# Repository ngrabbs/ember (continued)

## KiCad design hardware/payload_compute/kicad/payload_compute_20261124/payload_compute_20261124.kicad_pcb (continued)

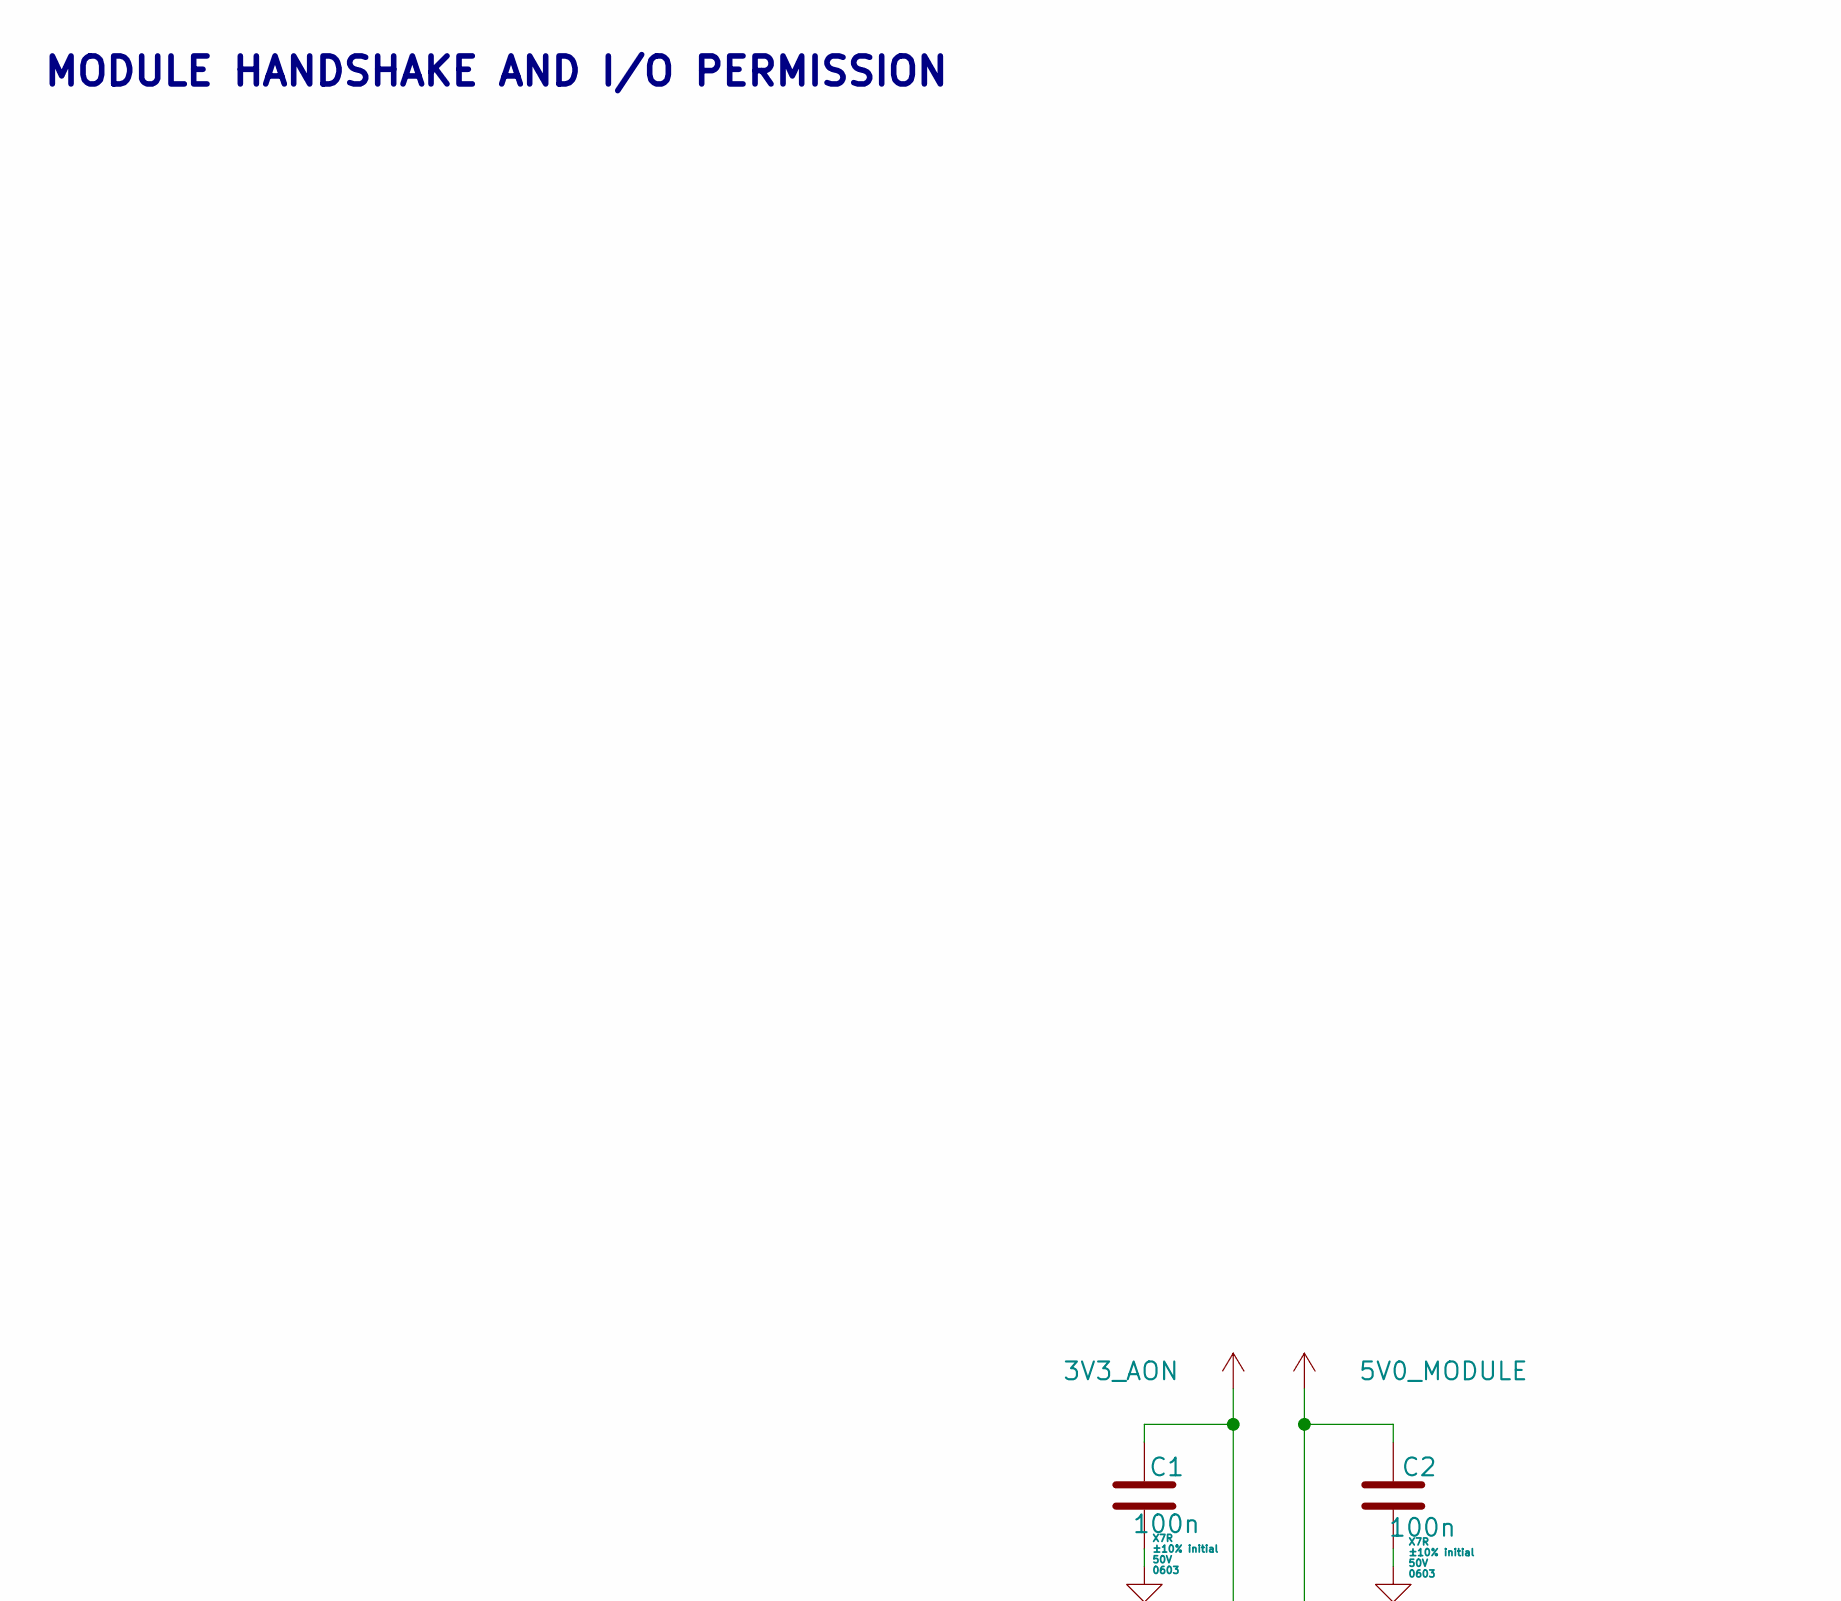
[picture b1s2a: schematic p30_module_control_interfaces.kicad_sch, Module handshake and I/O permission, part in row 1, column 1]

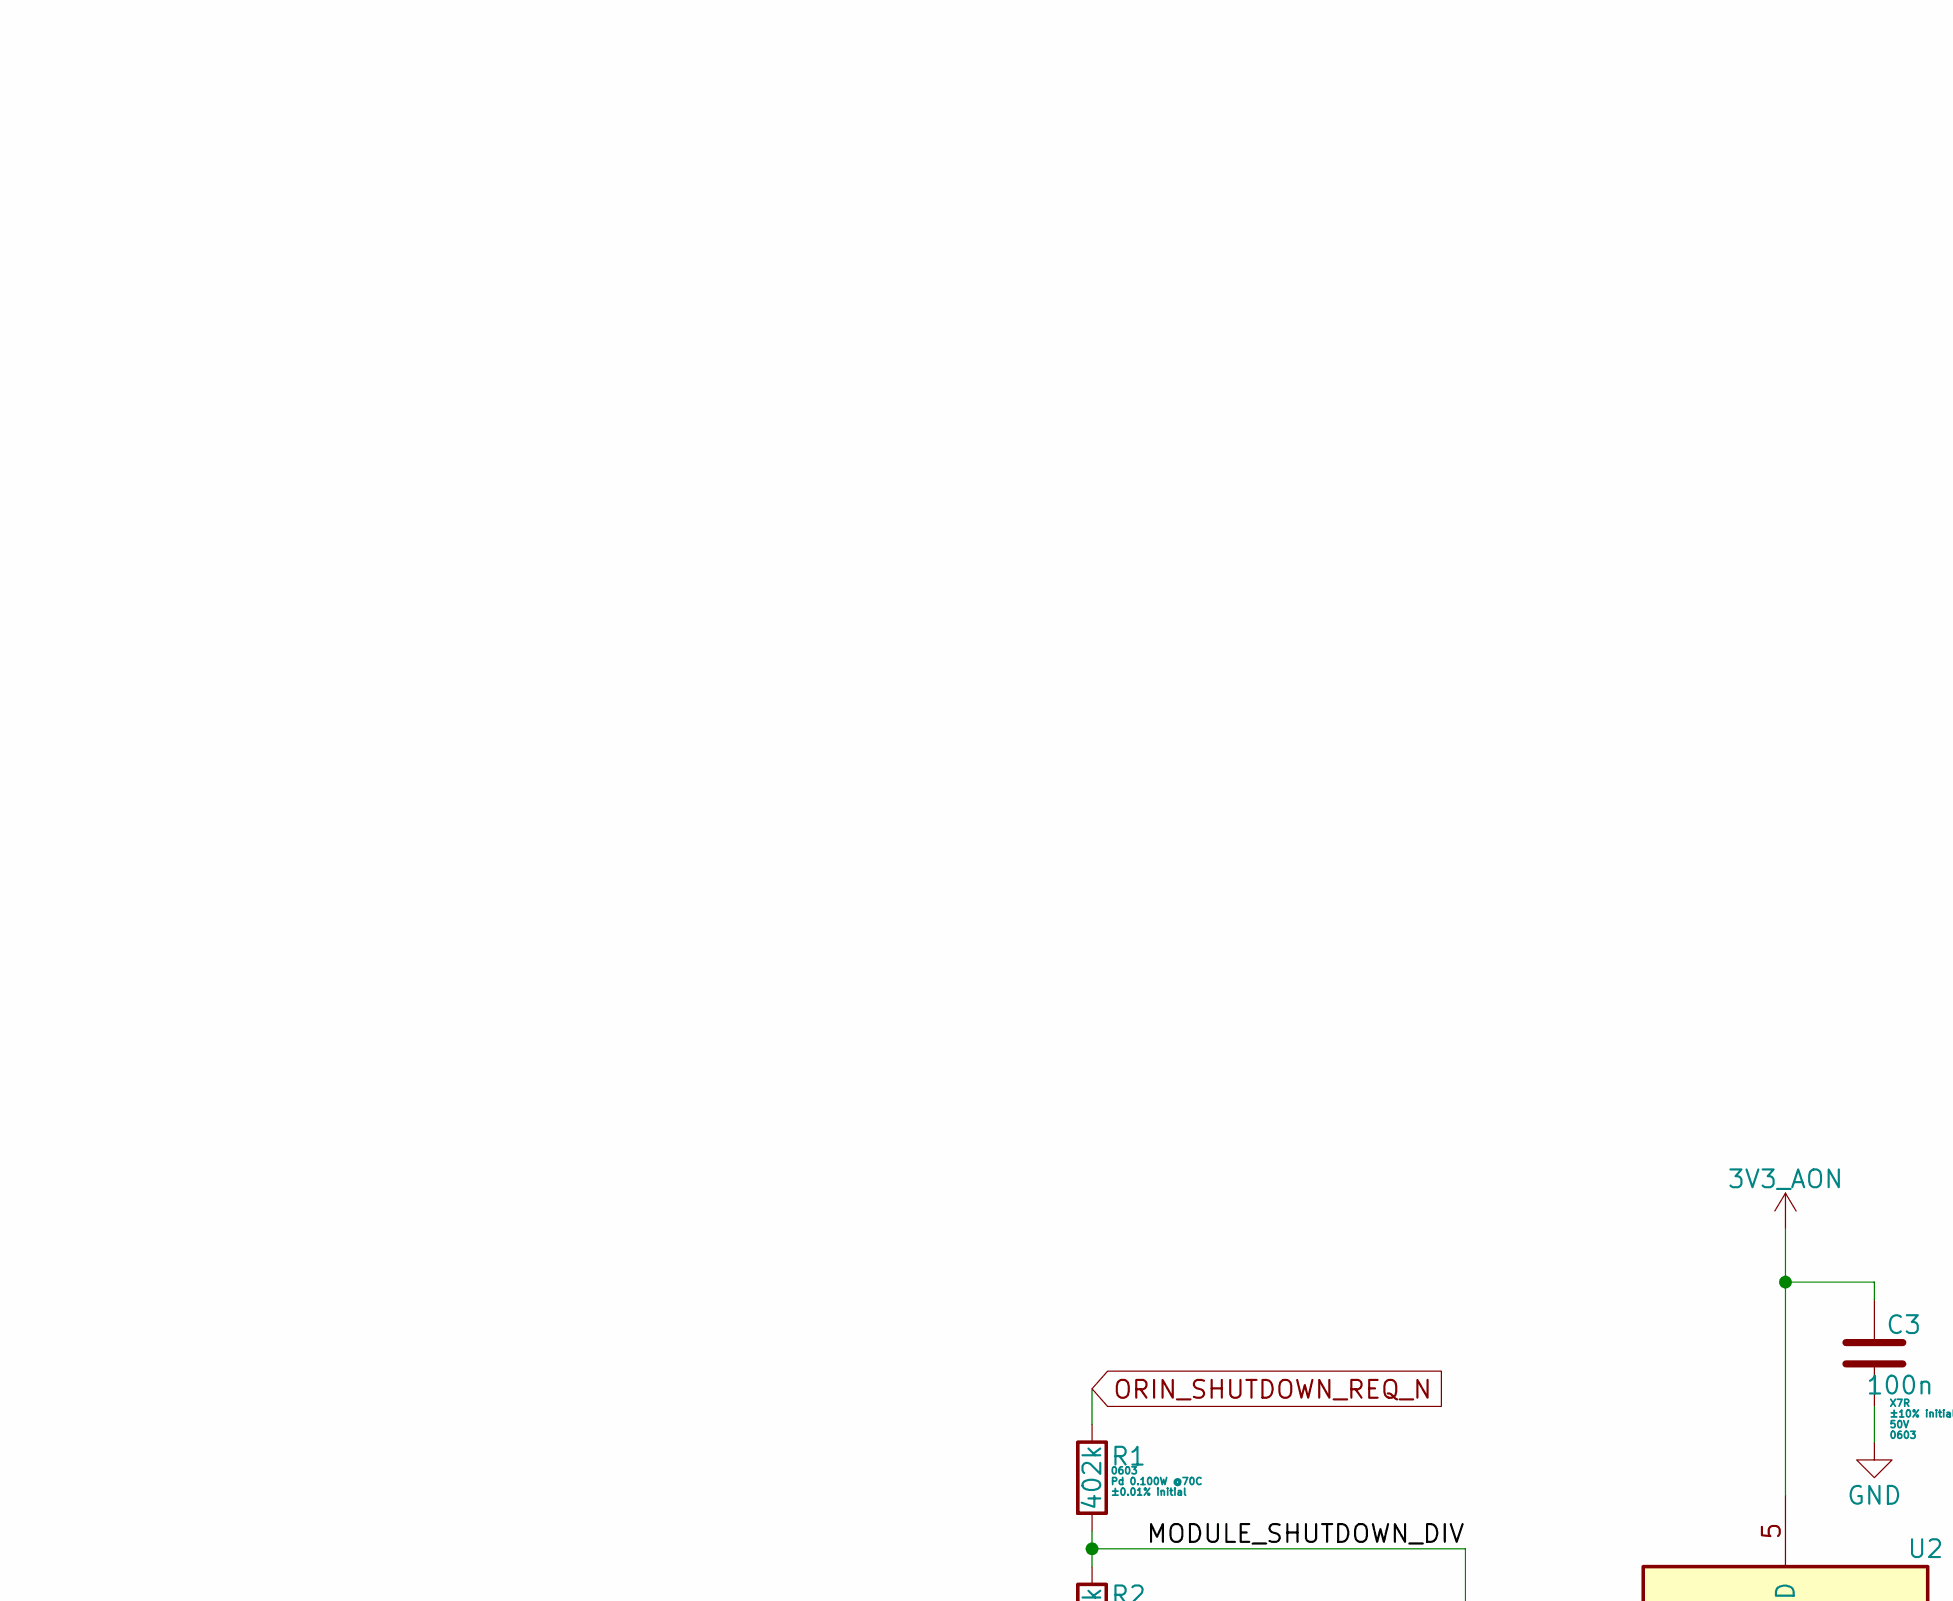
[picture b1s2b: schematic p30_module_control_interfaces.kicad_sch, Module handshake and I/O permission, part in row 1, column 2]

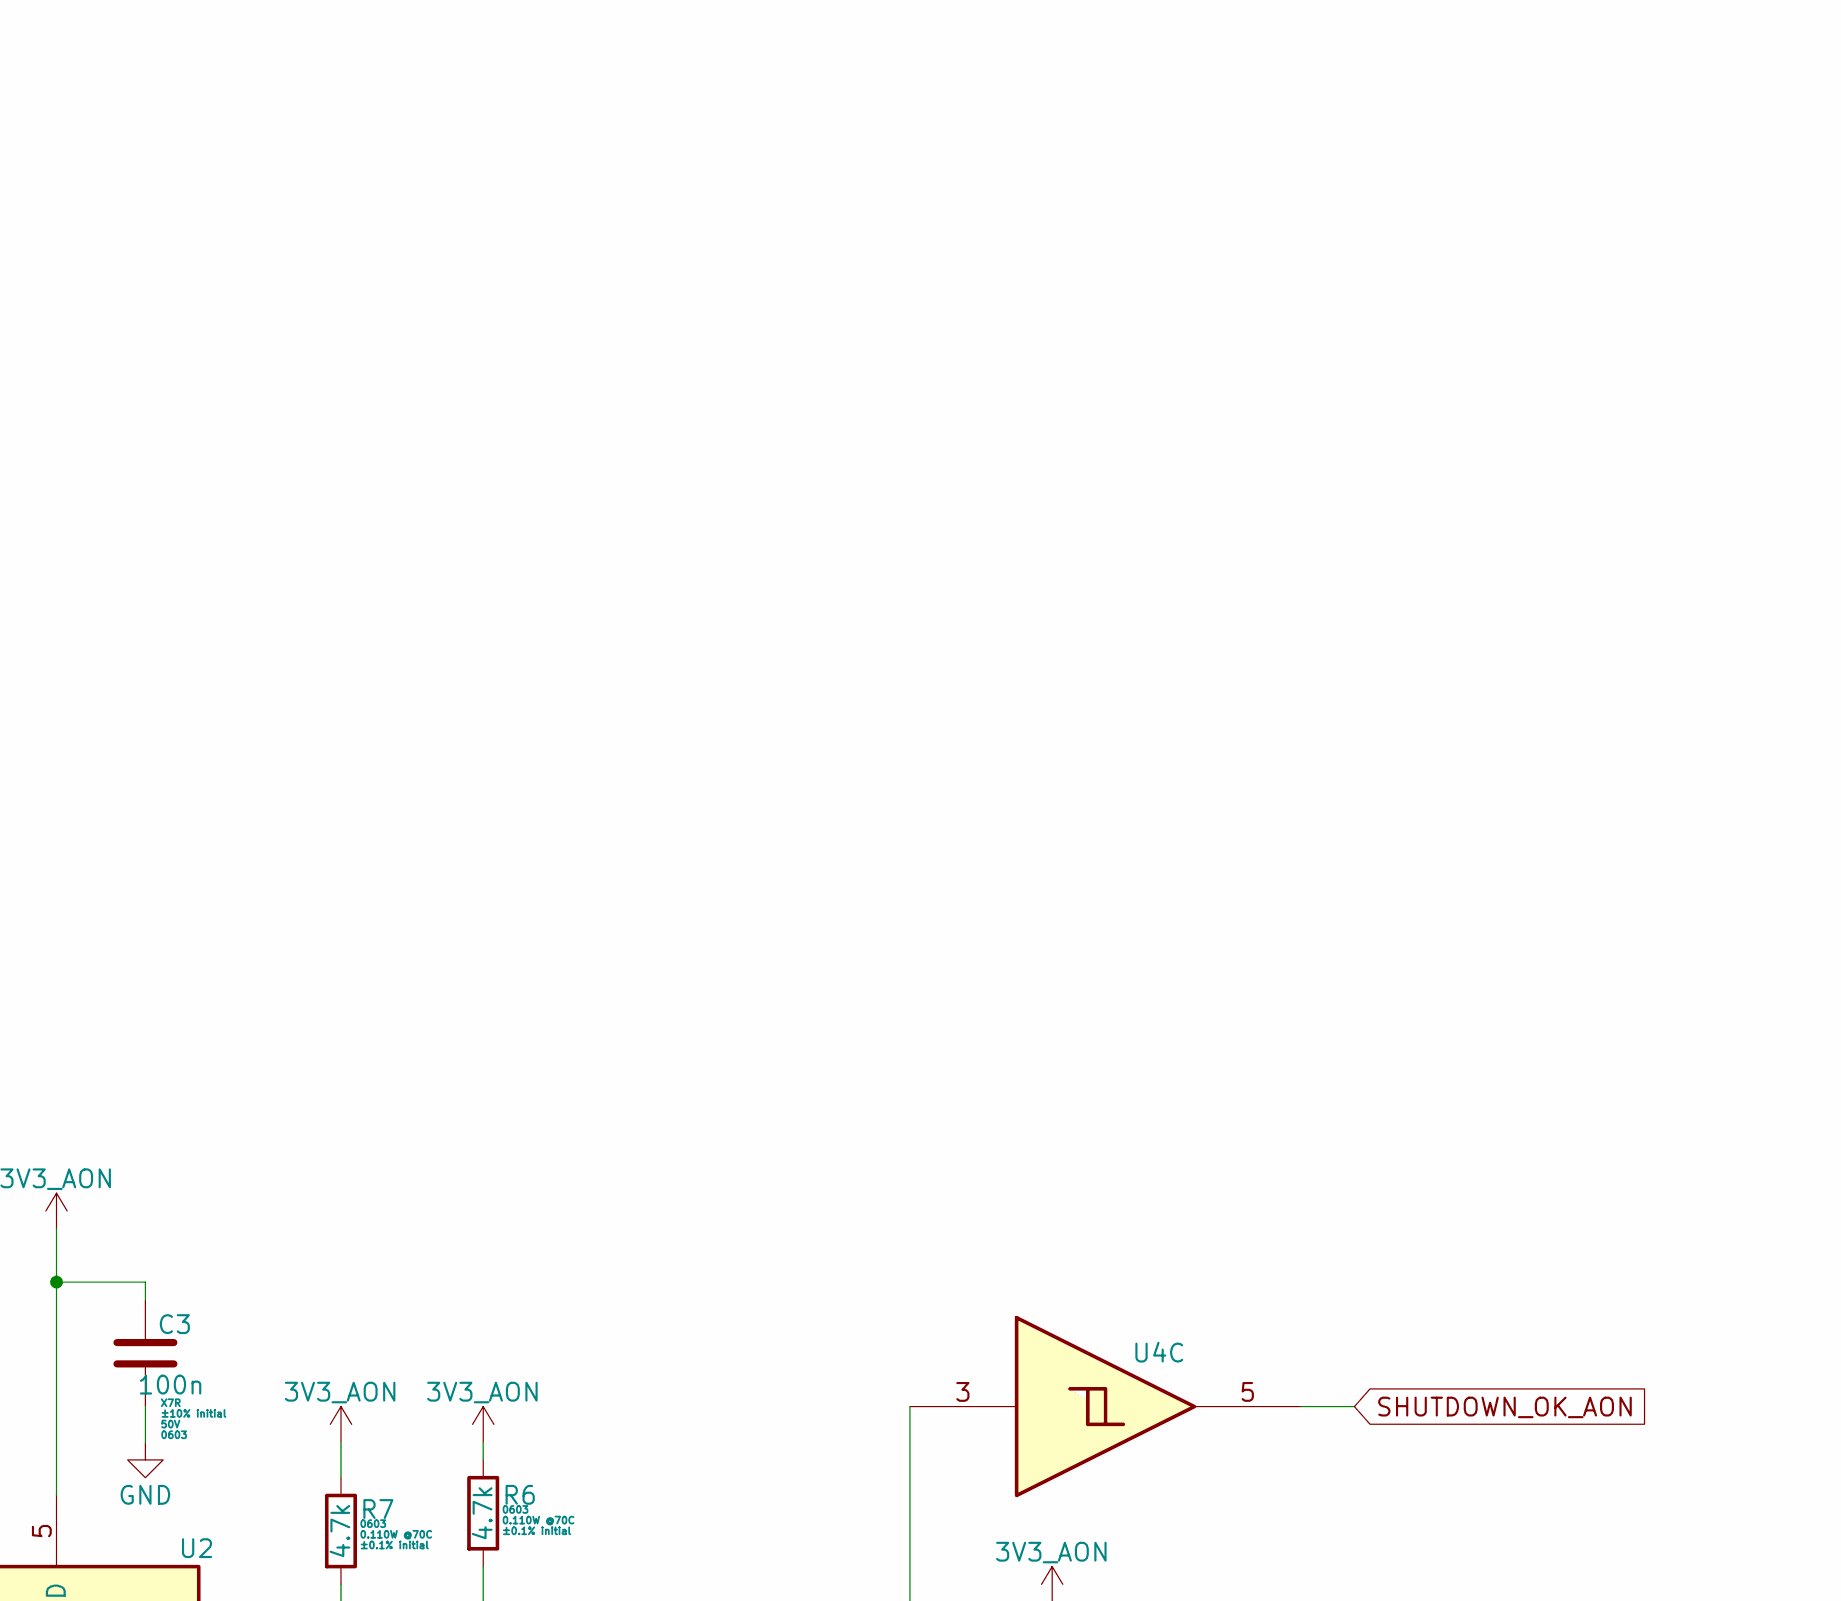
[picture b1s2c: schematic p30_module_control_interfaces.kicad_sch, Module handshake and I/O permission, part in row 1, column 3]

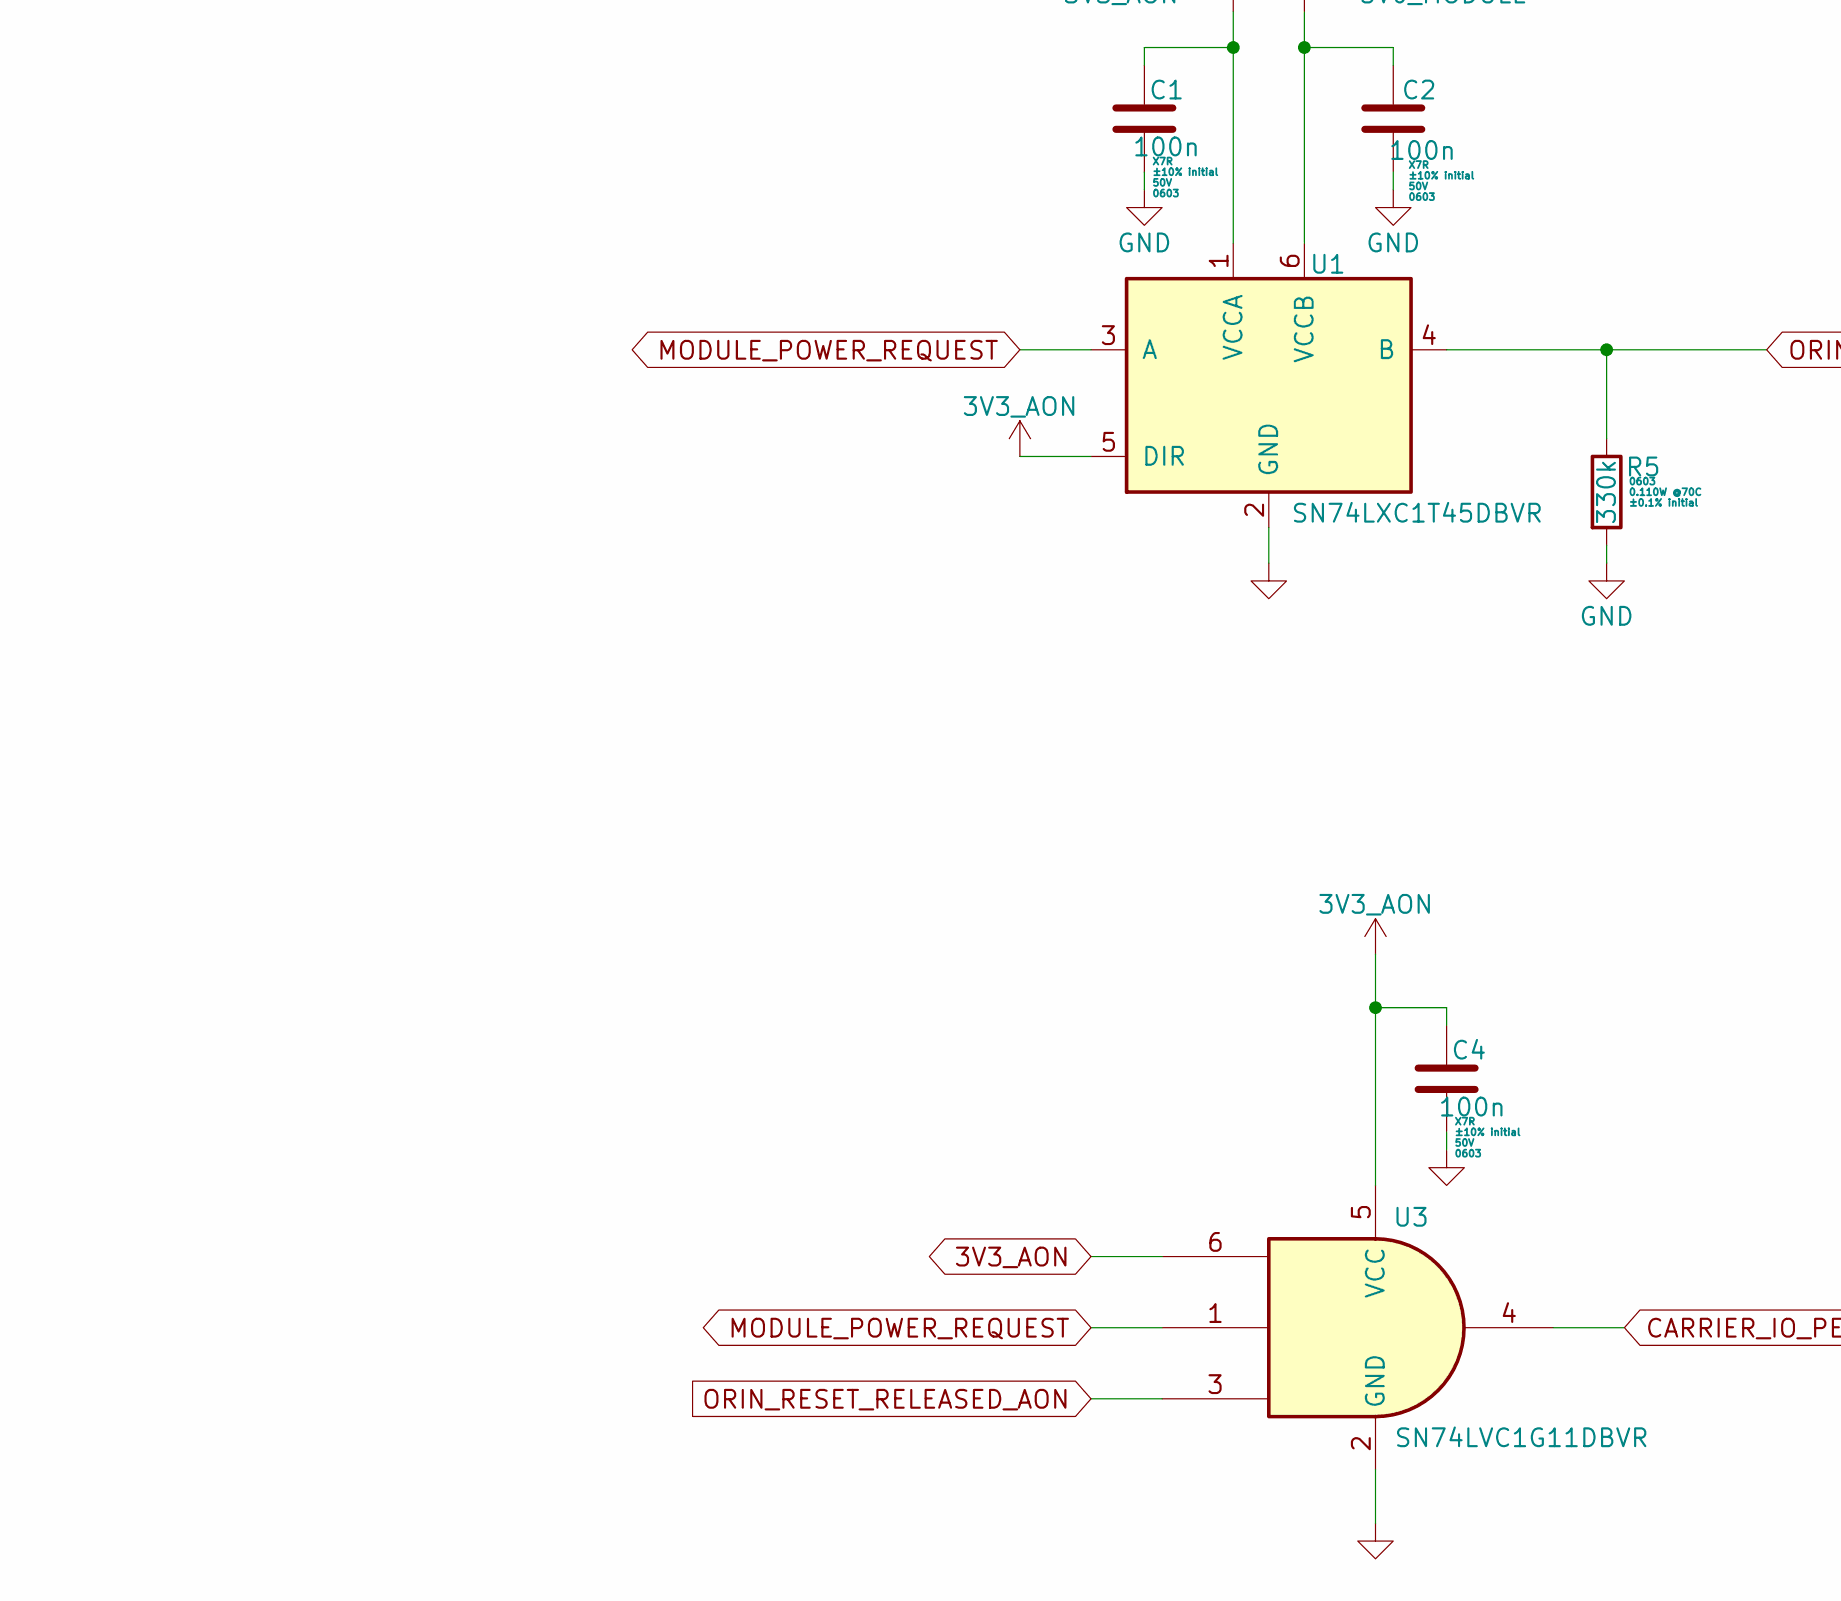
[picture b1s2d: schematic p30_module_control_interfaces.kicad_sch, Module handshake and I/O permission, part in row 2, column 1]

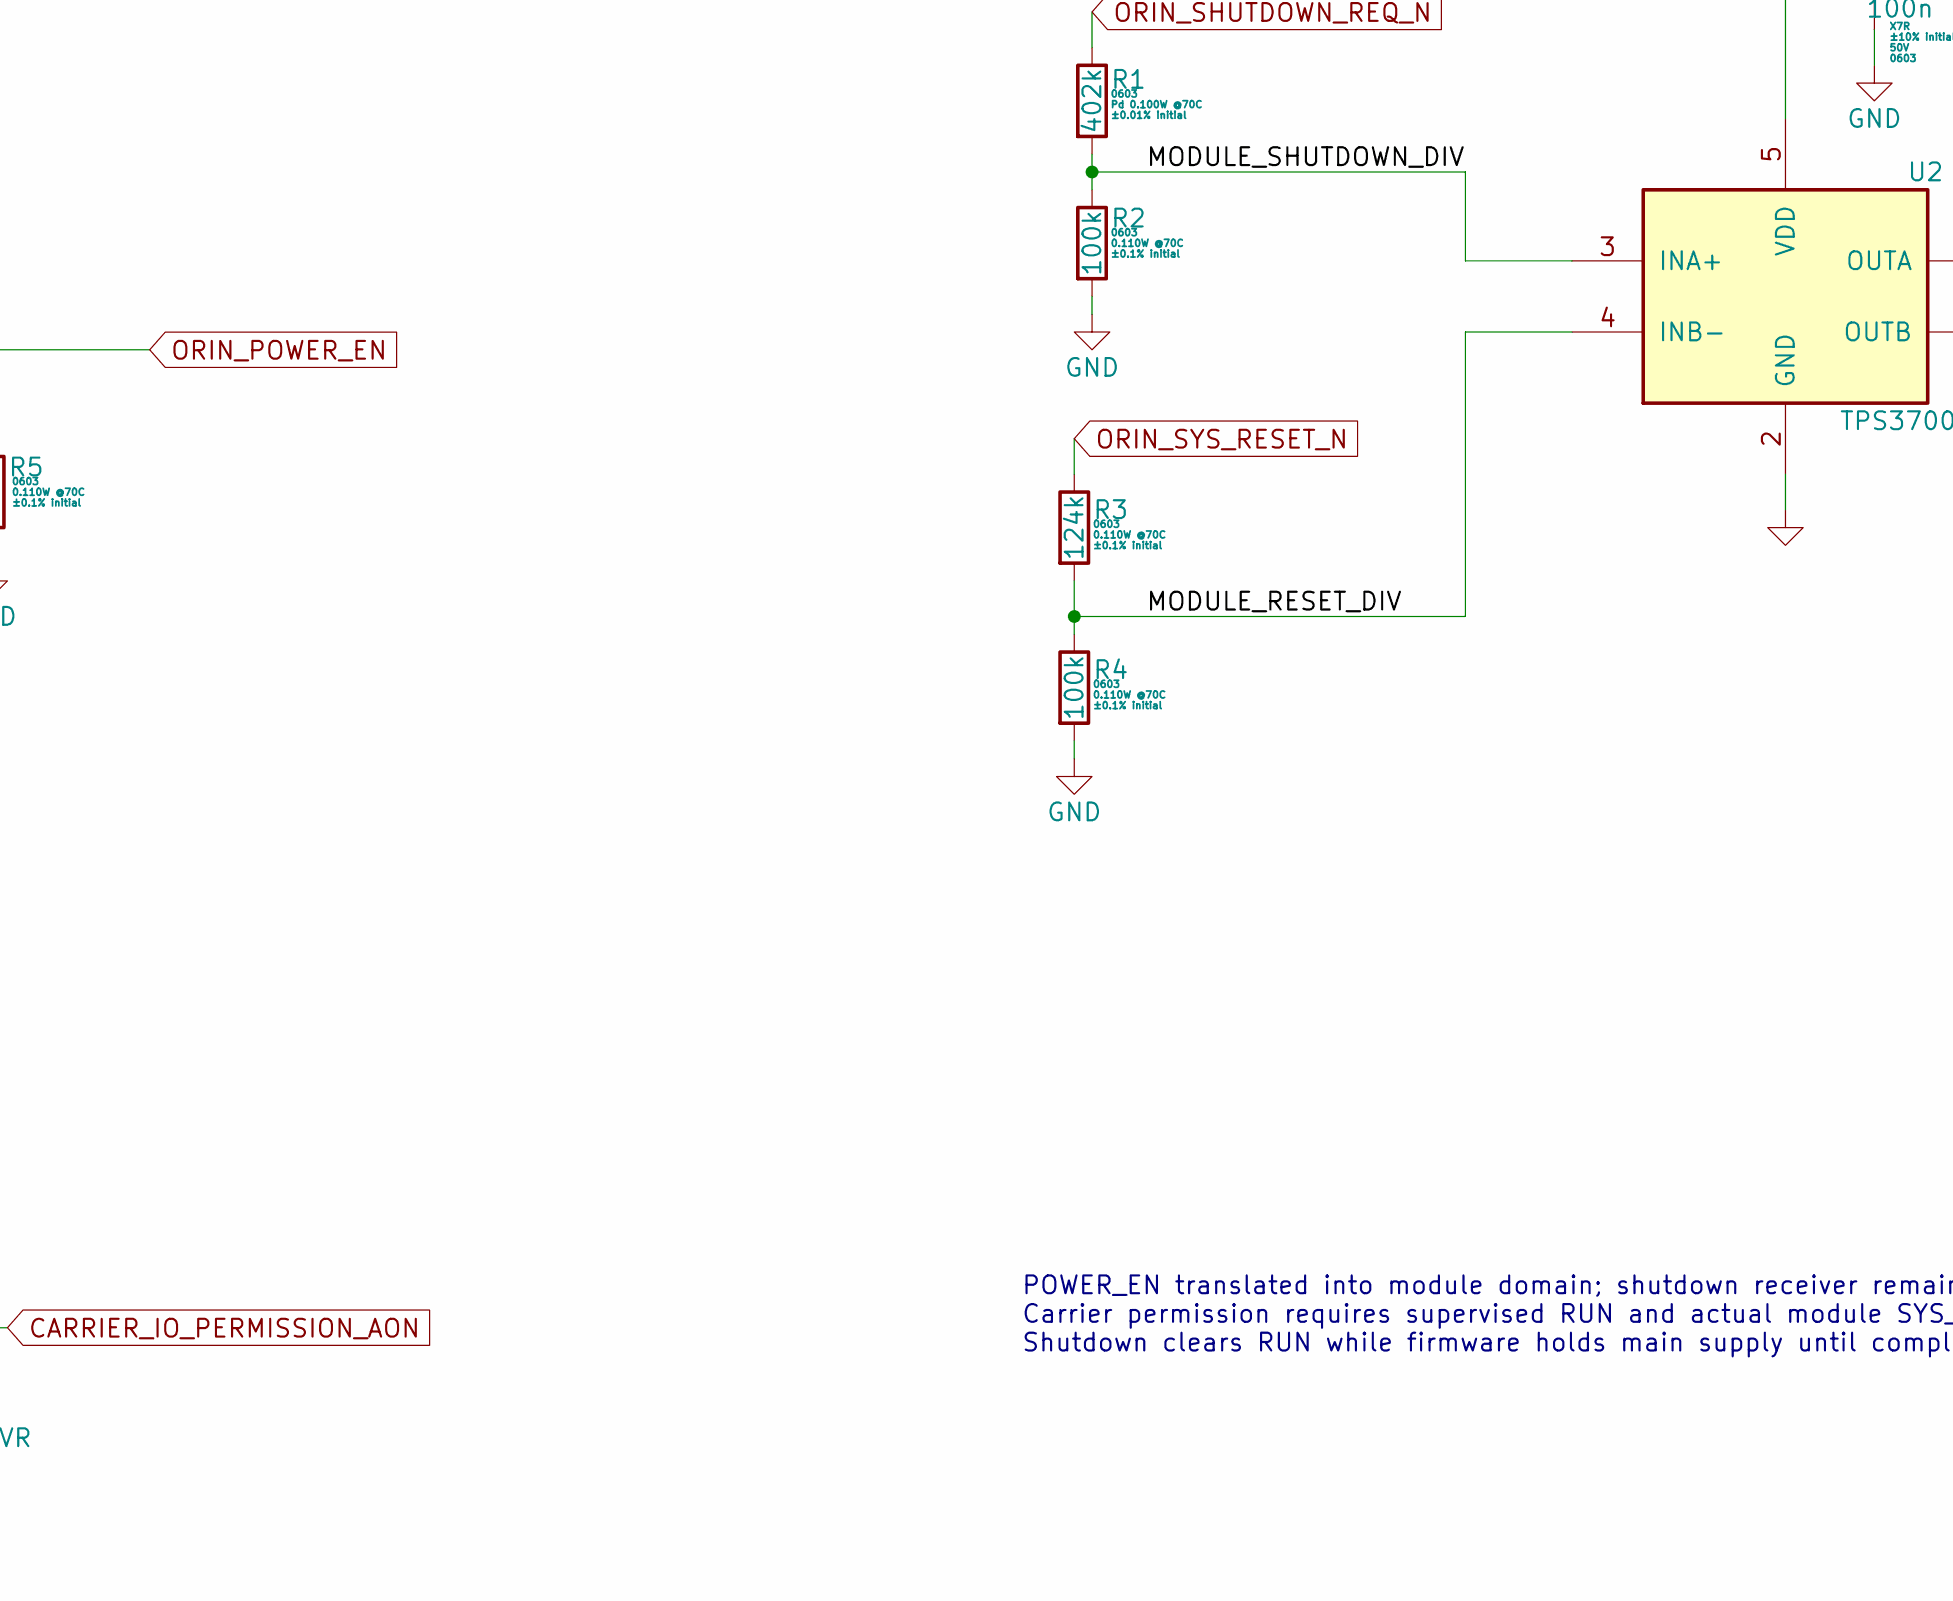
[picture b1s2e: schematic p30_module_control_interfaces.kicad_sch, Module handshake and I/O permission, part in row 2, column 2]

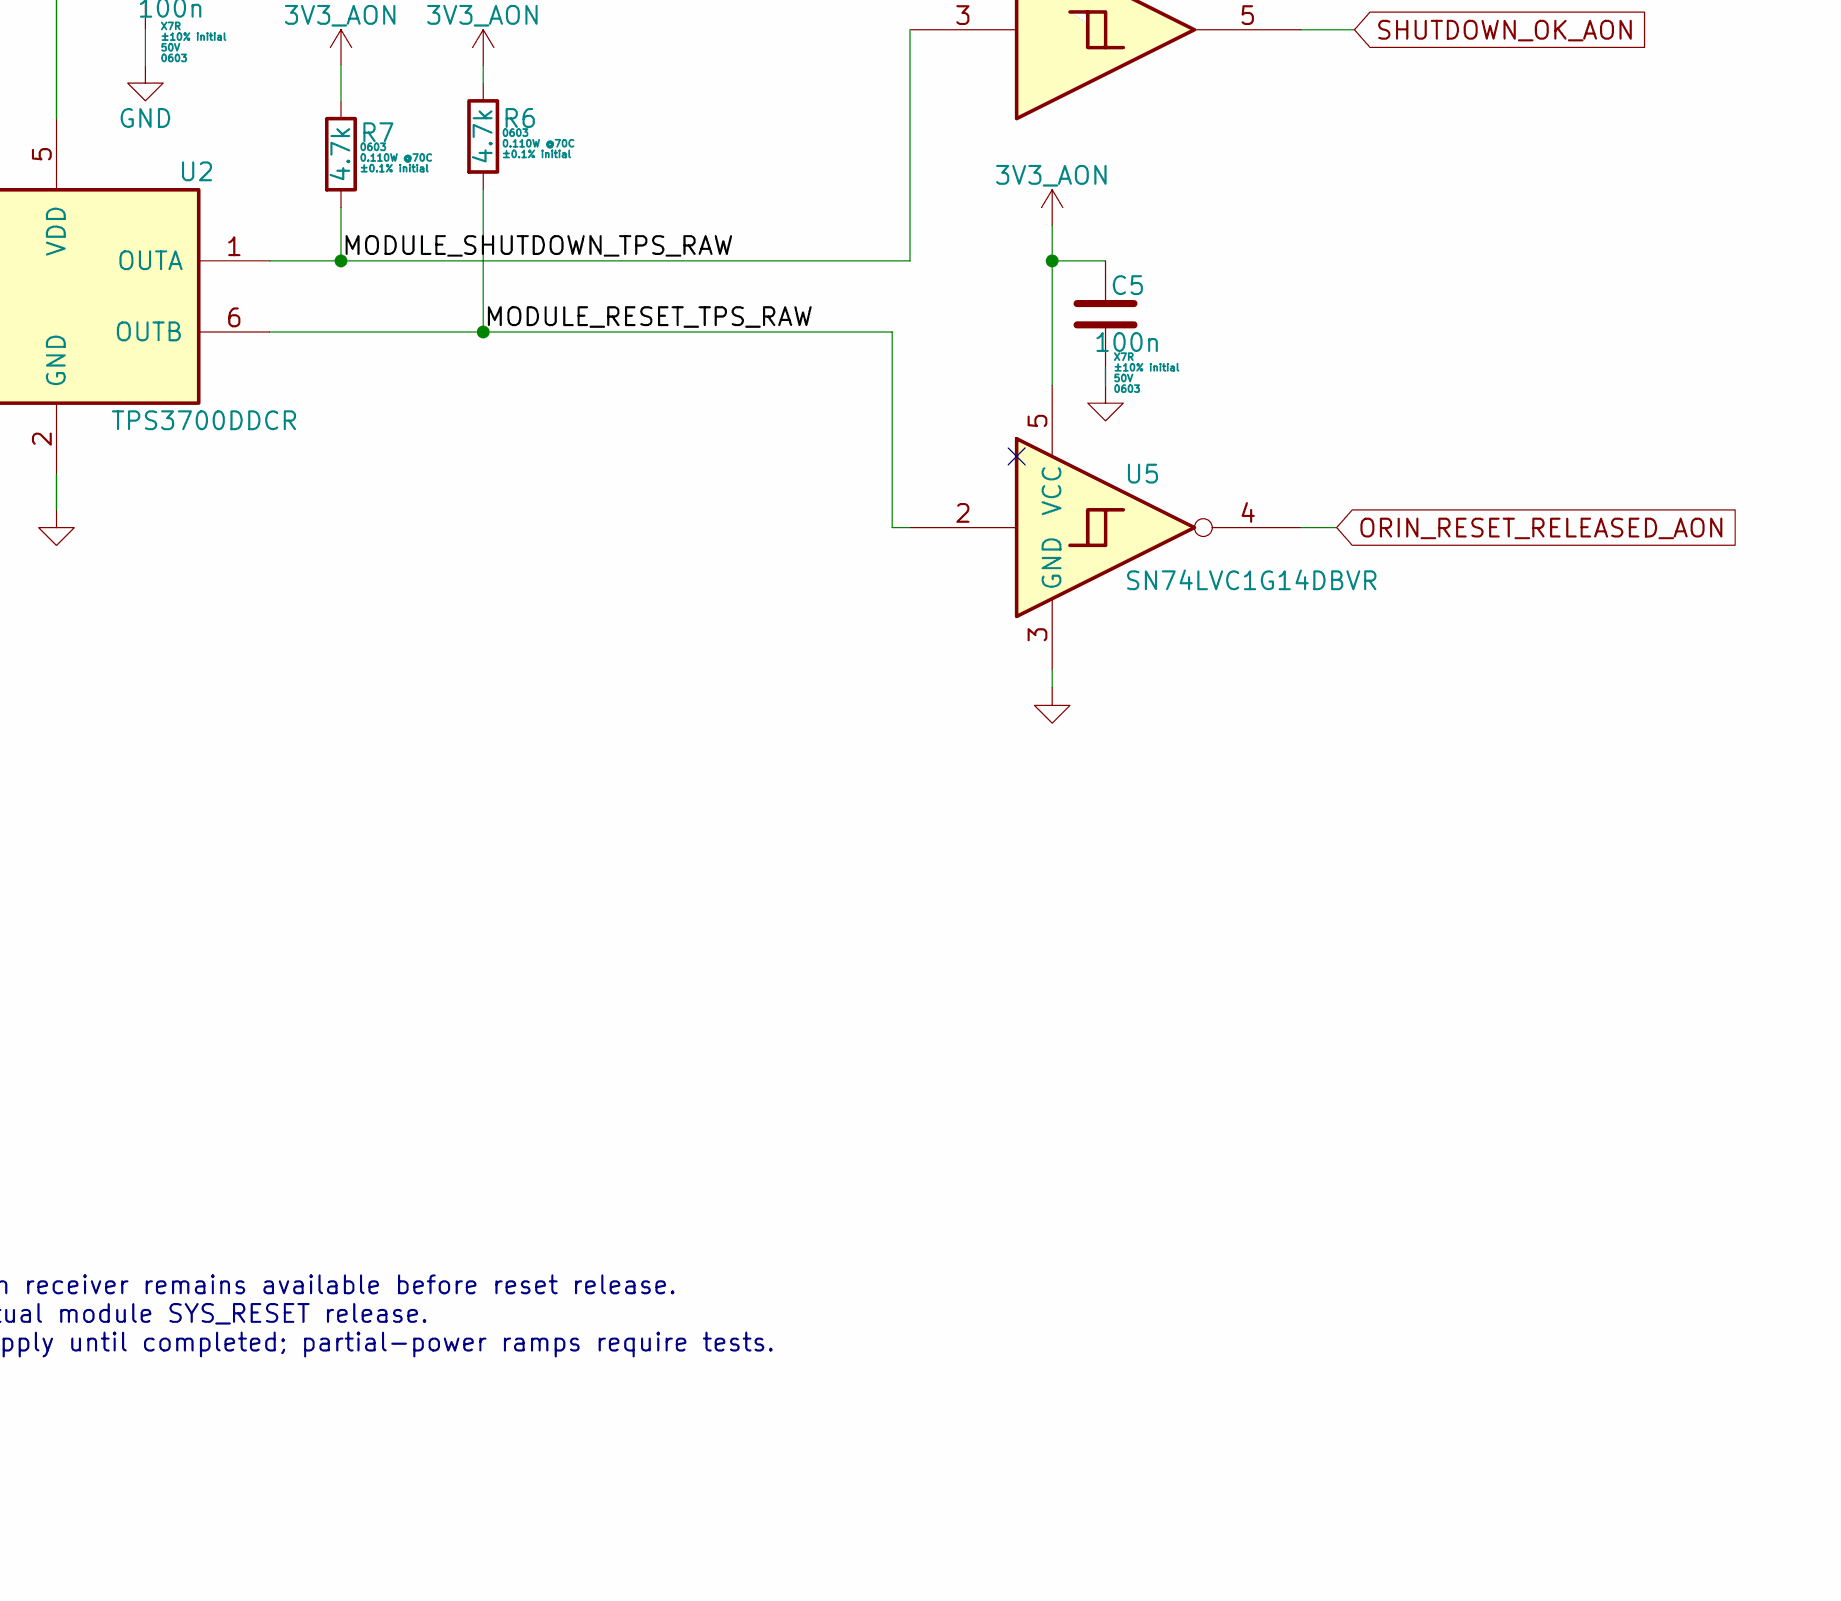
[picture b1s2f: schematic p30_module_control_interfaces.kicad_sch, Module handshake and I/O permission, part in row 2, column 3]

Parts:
C1, C2, C3, C4, C5: 100n; C_0603_1608Metric; Tolerance +/-10% initial; Voltage 50V; MFG P/N C0603C104K5RACTU
R1: 402k; R_0603_1608Metric; Tolerance +/-0.01% initial; MFG P/N P0603C4023LNT
R2, R4: 100k; R_0603_1608Metric; Tolerance +/-0.1% initial; MFG P/N TNPW0603100KBEEA
R3: 124k; R_0603_1608Metric; Tolerance +/-0.1% initial; MFG P/N TNPW0603124KBEEA
R5: 330k; R_0603_1608Metric; Tolerance +/-0.1% initial; MFG P/N TNPW0603330KBEEA
R6, R7: 4.7k; R_0603_1608Metric; Tolerance +/-0.1% initial; MFG P/N TNPW06034K70BEEA
U1: SN74LXC1T45DBVR; TI_DBV0006A_SOT23_6; MFG P/N SN74LXC1T45DBVR
U2: TPS3700DDCR; TI_DDC0006A_SOT23_THIN_6; MFG P/N TPS3700DDCR
U3: SN74LVC1G11DBVR; TI_DBV0006A_SOT23_6; MFG P/N SN74LVC1G11DBVR
U4: SN74LVC3G17DCUR; VSSOP-8_2.3x2mm_P0.5mm; MFG P/N SN74LVC3G17DCUR
U5: SN74LVC1G14DBVR; TI_DBV0005A_SOT23_5; MFG P/N SN74LVC1G14DBVR

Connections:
3V3_AON: C1.1, C3.1, C4.1, C5.1, R6.1, R7.1, U1.1 (VCCA), U1.5 (DIR), U2.5 (VDD), U3.5 (VCC), U3.6, U5.5 (VCC); also elsewhere on the board
5V0_MODULE: C2.1, U1.6 (VCCB); also elsewhere on the board
/Module handshake and I/O permission/MODULE_RESET_DIV: R3.2, R4.1, U2.4 (INB-)
/Module handshake and I/O permission/MODULE_RESET_TPS_RAW: R6.2, U2.6 (OUTB), U5.2
/Module handshake and I/O permission/MODULE_SHUTDOWN_DIV: R1.2, R2.1, U2.3 (INA+)
/Module handshake and I/O permission/MODULE_SHUTDOWN_TPS_RAW: R7.2, U2.1 (OUTA), U4.3
CARRIER_IO_PERMISSION_AON: U3.4; also elsewhere on the board
GND: C1.2, C2.2, C3.2, C4.2, C5.2, R2.2, R4.2, R5.2, U1.2 (GND), U2.2 (GND), U3.2 (GND), U5.3 (GND); also elsewhere on the board
MODULE_POWER_REQUEST: U1.3 (A), U3.1; also elsewhere on the board
ORIN_POWER_EN: R5.1, U1.4 (B); also elsewhere on the board
ORIN_RESET_RELEASED_AON: U3.3, U5.4
ORIN_SHUTDOWN_REQ_N: R1.1; also elsewhere on the board
ORIN_SYS_RESET_N: R3.1; also elsewhere on the board
SHUTDOWN_OK_AON: U4.5; also elsewhere on the board

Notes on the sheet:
MODULE HANDSHAKE AND I/O PERMISSION
POWER_EN translated into module domain; shutdown receiver remains available before reset release. Carrier permission requires supervised RUN and actual module SYS_RESET release. Shutdown clears RUN while firmware holds main supply until completed; partial-power ramps require tests.
